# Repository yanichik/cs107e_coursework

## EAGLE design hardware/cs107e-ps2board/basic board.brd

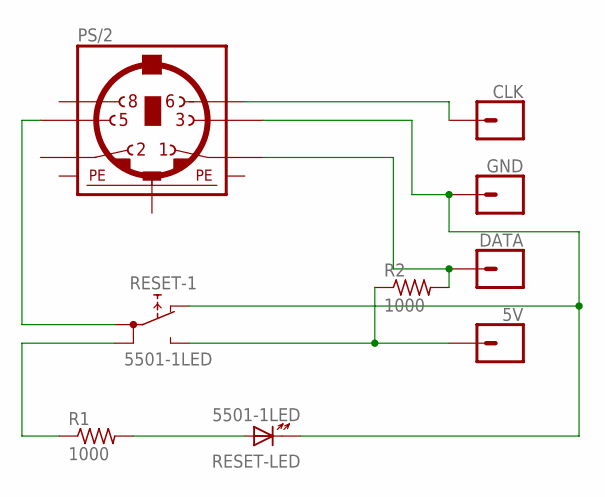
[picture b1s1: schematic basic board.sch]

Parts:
5V: 1X01
CLK: 1X01
DATA: 1X01
GND: 1X01
PS/2: M_DIN6
R1, R2: 1000; 0309/12
RESET: 5501-1LED

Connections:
GND: GND.1, PS/2.3, RESET.- (K), RESET.NC
unnamed: CLK.1, PS/2.6
unnamed: DATA.1, PS/2.1, R2.2
unnamed: PS/2.5, RESET.1A
unnamed: 5V.1, R2.1, RESET.NO
unnamed: R1.1, RESET.1B
unnamed: R1.2, RESET.+ (A)
PE1: PS/2.SH1 (PE1)
PE2: PS/2.SH2 (PE2)
PE3: PS/2.SH3 (PE3)

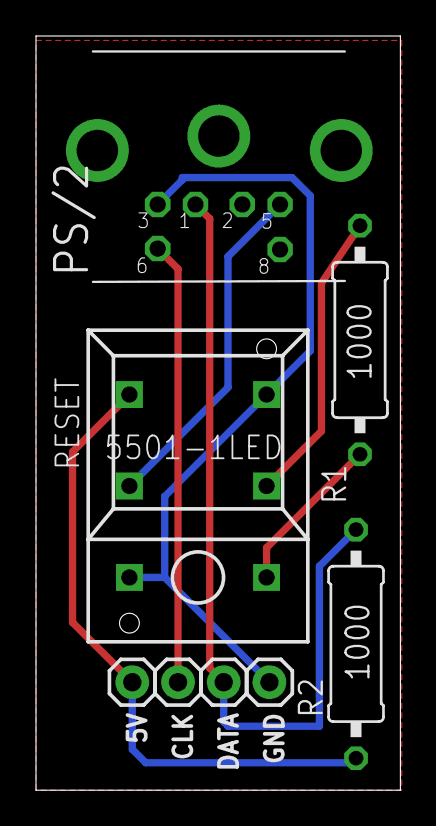
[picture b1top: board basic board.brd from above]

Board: 2 copper layers, 20.2 x 41.9 mm, 8 parts (0 on the bottom side), 7 nets.

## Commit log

2018-12-29 add README
2018-12-29 all files to repo

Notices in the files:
parts and their libraries:
SparkFun-Connectors: Licensing: Creative Commons ShareAlike 4.0 International - https://creativecommons.org/licenses/by-sa/4.0
